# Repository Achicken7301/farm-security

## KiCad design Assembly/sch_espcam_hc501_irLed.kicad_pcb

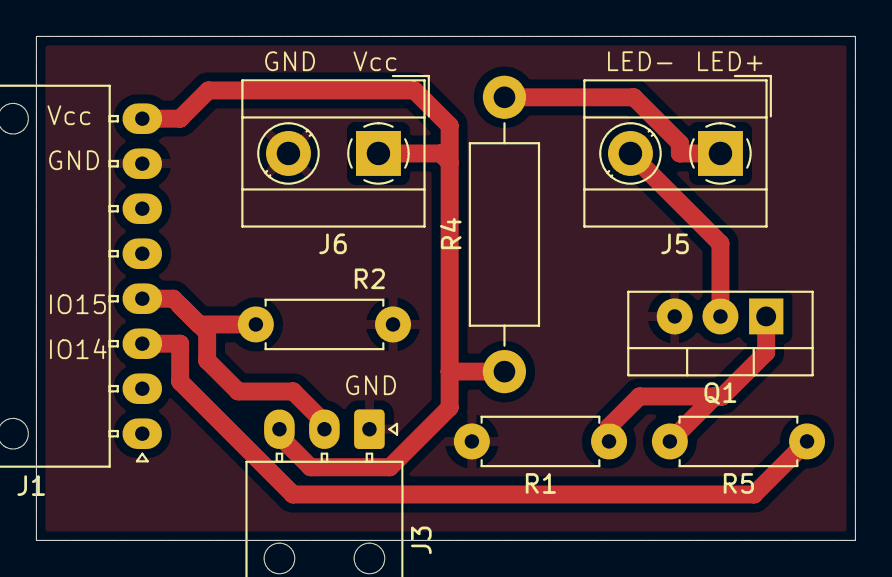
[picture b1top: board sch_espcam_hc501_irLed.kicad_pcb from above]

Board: 2 copper layers, 45.5 x 28.0 mm, 9 parts (0 on the bottom side), 7 nets.

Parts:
J1: Conn_01x08_Socket; Molex_Nano-Fit_105313-xx08_1x08_P2.50mm_Horizontal
J3: HC501; Molex_Nano-Fit_105313-xx03_1x03_P2.50mm_Horizontal
J5: IR_LED_850nm; TerminalBlock_MetzConnect_Type055_RT01502HDWU_1x02_P5.00mm_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
J6: POWER; TerminalBlock_MetzConnect_Type055_RT01502HDWU_1x02_P5.00mm_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
Q1: IRF540N; TO-220-3_Vertical
R1: 100k; R_Axial_DIN0207_L6.3mm_D2.5mm_P7.62mm_Horizontal
R2, R5: 1k; R_Axial_DIN0207_L6.3mm_D2.5mm_P7.62mm_Horizontal
R4: 5.6; R_Axial_DIN0411_L9.9mm_D3.6mm_P15.24mm_Horizontal

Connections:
/GPIO15: J1.4, J3.2, R2.2
Earth: J1.7, J3.1, J6.2, Q1.3 (S), R1.2, R2.1
GPIO14: J1.3, R5.1
unnamed: J5.1, R4.2
unnamed: J5.2, Q1.2 (D)
unnamed: Q1.1 (G), R1.1, R5.2
VCC: J1.8, J3.3, J6.1, R4.1

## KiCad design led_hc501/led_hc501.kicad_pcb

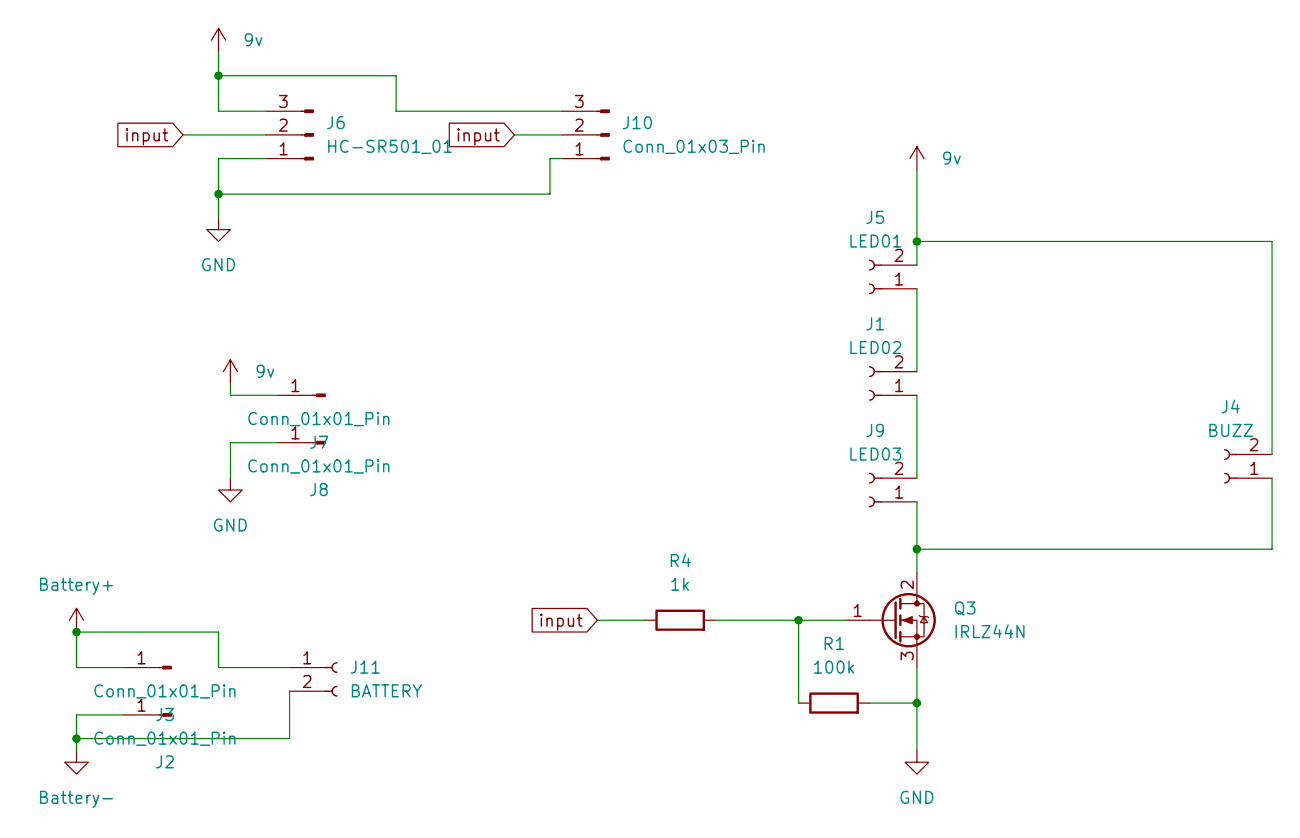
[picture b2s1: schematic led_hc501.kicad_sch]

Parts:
J1: LED02; JST_XH_B2B-XH-A_1x02_P2.50mm_Vertical
J2, J3, J7, J8: Conn_01x01_Pin; PinHeader_1x01_P2.54mm_Vertical
J4: BUZZ; JST_XH_B2B-XH-A_1x02_P2.50mm_Vertical
J5: LED01; JST_XH_B2B-XH-A_1x02_P2.50mm_Vertical
J6: HC-SR501_01; PinHeader_1x03_P2.54mm_Horizontal
J9: LED03; JST_XH_B2B-XH-A_1x02_P2.50mm_Vertical
J10: Conn_01x03_Pin; JST_XH_B3B-XH-A_1x03_P2.50mm_Vertical
J11: BATTERY; JST_XH_B2B-XH-A_1x02_P2.50mm_Vertical
Q3: IRLZ44N; TO-220-3_Vertical
R1: 100k; R_Axial_DIN0309_L9.0mm_D3.2mm_P2.54mm_Vertical
R4: 1k; R_Axial_DIN0309_L9.0mm_D3.2mm_P2.54mm_Vertical

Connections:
9v: J4.2, J5.2, J6.3, J7.1, J10.3
Battery+: J3.1, J11.1
Battery-: J2.1, J11.2
GND: J6.1, J8.1, J10.1, Q3.3 (S), R1.2
unnamed: J1.1, J9.2
unnamed: J1.2, J5.1
unnamed: J4.1, J9.1, Q3.2 (D)
unnamed: Q3.1 (G), R1.1, R4.2
input: J6.2, J10.2, R4.1

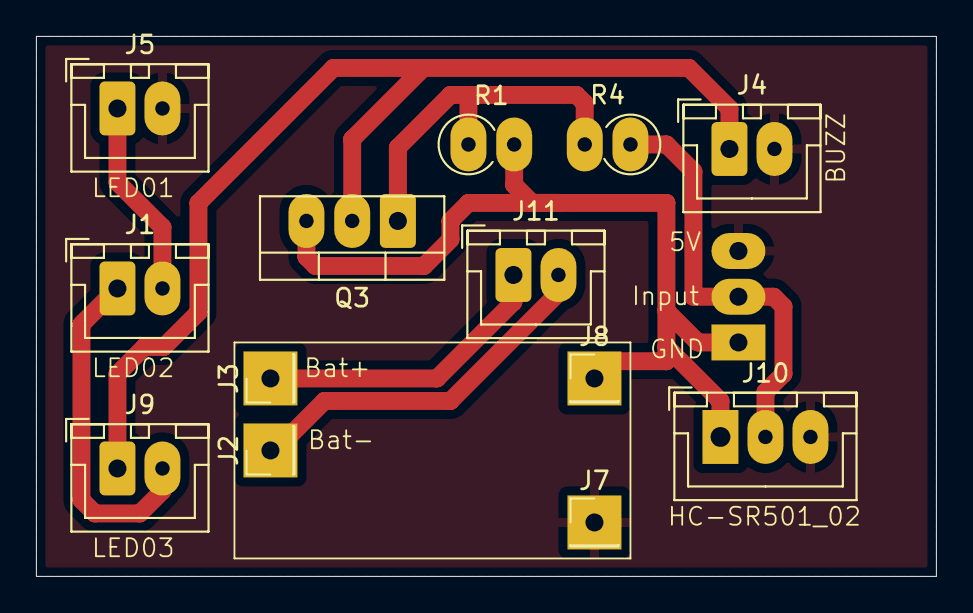
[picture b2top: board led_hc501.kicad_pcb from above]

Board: 2 copper layers, 50.0 x 30.0 mm, 14 parts (1 on the bottom side), 9 nets.

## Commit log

2024-02-01 init commit
2024-02-01 [Docs] Update docs
2024-02-02 [Docs] Edit readme file
2024-02-02 [Test] ESP-MESH
    Test esp mesh with 1 root and 1 child
2024-02-02 [Test] Test wifi softAP + STA
2024-02-04 [Test] Add esp-mesh
2024-02-06 [test] wifi+tcp_server
2024-02-08 [test] only works with correct ssid and pass
    If wrong SSID or PASS word, the system will crash. I need to fix this in the future, but know its not crucial.
2024-02-08 [test] scan for wifi
    Scan wifi and auto-connect is much better than config httpd manualy. I need some of the flash memory to by pass the httpd manual config.
2024-02-23 [test] mesh
2024-02-23 [feat] Update esp32 firmware
    Add mutiples modules (fsm), currently, fsm_http_server is NOT working.
    - fsm_tcp_server is an alternative for this, create tcp server at port 5544, then user can login using telnet or netcat. fsm_ap is a support fsm for fsm_tcp_server
    - scheduler.h is an simple scheduler implement using timer O(n) complexity.
    - fsm_mesh is needed for communicate betweent multples esp32.
2024-02-27 [feat] root connect to internet through tcp socket
2024-03-04 [feat] Camera to tcp_server
    Import esp_cam.h module,
    take frame as jpeg send to simple tcp_server created by python.
2024-03-04 [docs] Update document
2024-03-04 [feat] Exactly the previous nothing special
2024-03-05 [test] Serperate each module
2024-03-06 [test] camera http client
    camera send data to server throught http client, instead of tcp socket.
2024-03-08 [feat] Seperate dir for cam and root
    For Esp-root will work on:
    - receiving mesh
    - use http client send data receive from mesh
    for Esp-cam will work on:
    - take image data
    - send to root via mesh network
2024-03-09 [feat] from camera to http server
    Using malloc (i WILL NOT use malloc in production code)
2024-03-09 [fxi] Fix conflict timer0 group0
    GROUP0_TIMER0 is used by some services like http client or mesh or something i dont know. Change timer fix the problem.
2024-03-09 [Fix] No need allocate memory cause many crashes
2024-03-10 [test] Add folder used for no external ram
2024-03-10 [feat] I_AM_ROOT module
    - just simply forgo the election process before scan
2024-03-29 [test] no idea
2024-04-03 [SCHEMATIC] testing
